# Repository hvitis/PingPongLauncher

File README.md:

# Ping Pong Launcher

A static website with four launcher tabs: the supplied 3D-printed launcher, [codyhsu’s Arduino launcher](https://www.mobile01.com/topicdetail.php?f=696&t=5867234), PingPongThrower (Pico 2 W), and [Nguyen Van Hien’s Bluetooth Table Tennis Robot](https://www.youtube.com/watch?v=-pSiuAdUKP4).

The original launcher has a complete build guide. It includes English source translations, an interactive Three.js CAD viewer, a 13-step animated assembly wizard, a parts list, and printable model downloads.

**Build status:** documented prototype. The source includes a physical prototype, but this English guide has not been validated through a complete build. Resolve the [open build questions](docs/build-notes.md) before ordering or operating the hardware.

## How the ball-throwing mechanism works

The launch energy comes from **two motor-driven, rubber-covered wheels**. Their rotating mass stores energy. Friction transfers some of that energy to the ball when it passes between their rims.

The “exhaust” is the **outlet tube**. It guides the ball toward the wheel contact region and the exit. The wheels provide the throwing force.

```mermaid
flowchart LR
    H[Hopper: gravity feeds balls] --> F[Geared feed screw: advances balls]
    F --> S[Stopper: holds the following ball]
    S --> W[Two rubber-covered wheels: accelerate one ball]
    W --> O[Outlet: ball leaves toward the table]
    C1[Left PWM control] --> W
    C2[Right PWM control] --> W
    C3[Feed PWM control] --> F
```

1. **The hopper stores the balls.** Gravity brings a ball to the feed opening.
2. **The geared motor turns the feed screw.** The screw advances balls toward the launch head.
3. **The stopper separates consecutive balls.** It helps prevent one ball from dragging the following ball into the wheels.
4. **The two wheel surfaces grip the ball.** Both contact surfaces move toward the exit, although the wheels rotate in opposite directions.
5. **The ball accelerates through friction.** Rubber improves traction and provides compliance at contact.
6. **The ball leaves the wheel contact region.** Its momentum carries it forward. The tilt angle sets the initial launch direction.

The feeder meters balls into the launch region. It is separate from the wheel mechanism that supplies launch energy. The feeder PWM mainly changes the feed interval. The other two PWM controls change the two launch motors independently.

### Speed, grip, and spin

A wheel’s rim speed depends on its radius and measured rotational speed:

```text
rim speed v = 2 × π × wheel radius r × rpm / 60
```

Use meters for `r` to obtain meters per second. The real exit speed also depends on contact pressure, rubber, slip, wheel inertia, motor torque, and speed loss during a shot. A PWM knob position is not a measured rpm or ball speed.

For an ideal pair of opposing, parallel wheel contacts with no slip, ball translation is approximately the average of the two contact speeds. The difference produces spin:

```text
ideal ball speed ≈ (v1 + v2) / 2
ideal spin rate  ≈ (v1 - v2) / (2 × ball radius)  [radians per second]
```

These equations describe a simplified contact model, not a calibrated prediction for this CAD. Actual contact angles, rubber compression, and slip change the result. Similar contact speeds reduce differential spin in that model. Unequal speeds add spin about the axis determined by the wheel arrangement.

The source does not specify the final rubber thickness, wheel gap, motor rpm, exit speed, or spin calibration. Measure those values during a guarded physical build. [The website](docs/index.html) explains the ball path alongside the model.

## Start the local website

Use Node.js 22 or newer. The website and development server require **no package installation**.

```sh
make serve
```

Open **http://127.0.0.1:4173**. `make serve` regenerates and validates the current site before opening the preview server. The server watches `docs/` and reloads the browser after a change. An edit to `docs/data/project.json` also regenerates the written guide and BOM.

```sh
make serve PORT=4200   # choose another local port
make build             # regenerate, check, and export dist/
make check             # regenerate and validate current content
npm run check        # check content, links, inventory, and GLB structure
npm run build        # regenerate documentation and copy the site to dist/
```

The local server binds to `127.0.0.1` by default. The exported site has no server requirement. All Three.js modules, models, photos, and fonts are local; there are no runtime CDN requests.

## Arduino launcher study

Open `?launcher=mobile01` to link directly to the second tab. Arrow keys, Home and End switch tabs; the URL supports reload and browser Back/Forward. Old section links still open the printed launcher.

Read [the analysis and design notes](docs/mobile01-analysis.md). The new diagrams explain the mechanism and a proposed electrical arrangement; they do not claim original CAD dimensions or verified original GPIO assignments. The KiCad download is an **unrouted placement draft**, with pads and named nets. It has no fabrication outputs and has not passed KiCad DRC or a physical build.

`docs/data/mobile01.json` records the parts and proposed connection map. The matching table and CSV files are maintained alongside it. Regenerate the three SVG diagrams, PCB and pad netlist with `python3 scripts/create-mobile01-assets.py`; the normal Node-only build uses the checked-in outputs.

## Bluetooth table tennis robot study

Open `?launcher=hien` to link directly to the fourth tab (Nguyen Van Hien's project).

Read [the technical analysis report](docs/hien-analysis.md). The tab features:
- **Interactive mechanism exploration:** 5-step animated ball flow showing bucket gravity fill, agitator stirring, servo escapement metering, curved feed drop, DT750 twin-flywheel launch, and pan/tilt trajectory vectoring.
- **Shot mode & spin comparison:** 4 practice drills (Service, Attack, Backspin Chop, Oscillating Swing) reconstructed from the creator's custom iOS BLE app.
- **Synchronized BOM & Wiring tables:** 21 parts with evidence ratings, and 14 connection rows downloadable as CSVs (`docs/downloads/hien-parts.csv` and `docs/downloads/hien-connections.csv`).
- **Vector technical diagrams:** Native SVGs for the mechanism (`docs/assets/hien/mechanism.svg`), electrical schematic with ATX split power rails and Mega GPIO assignments (`docs/assets/hien/schematic.svg`), and KiCad breakout board placement (`docs/assets/hien/pcb.svg`).
- **Unrouted KiCad placement draft:** 85 × 60 mm dual-layer board (`docs/downloads/hien-servo-breakout.kicad_pcb`) and netlist CSV (`docs/downloads/hien-pcb-netlist.csv`). Regenerate assets using `python3 scripts/create-hien-assets.py`.

## Build the launcher

Start with [the full English assembly guide](docs/assembly-guide.md). Use the website wizard to explore the CAD groups and track your checks on the current device.

| Build resource                           | File                                                                                       |
| ---------------------------------------- | ------------------------------------------------------------------------------------------ |
| Shopping checklist                       | [Website-ready checklist](docs/shopping-list.md) · [CSV](docs/downloads/shopping-list.csv) |
| Hardware and tools                       | [English BOM](docs/hardware-bom.md) · [CSV](docs/downloads/hardware-bom.csv)               |
| Component image sources                  | [Photo references and rights](docs/component-image-sources.md)                             |
| Print settings, orientations, and plates | [Print guide](docs/print-guide.md)                                                         |
| English print project                    | [28 objects on 10 plates](docs/downloads/launcher-english.3mf)                             |
| Individual STL files                     | [ZIP, organized by plate](docs/downloads/launcher-stl-pack.zip)                            |
| Editable CAD                             | [STEP assembly](docs/downloads/launcher-assembly.step)                                     |
| Wiring and first power-on                | [DC topology and checks](docs/wiring-guide.md)                                             |
| English annotations and terminology      | [Source translation](docs/translation.md)                                                  |
| Offline written instructions             | [Guide ZIP with reference photos](docs/downloads/english-build-guide.zip)                  |
| Missing details and source differences   | [Build notes](docs/build-notes.md)                                                         |

The source specifies two 12 V 550 motors, one 12 V / 77 rpm geared motor, three PWM controllers, four 7 × 16 × 5 mm bearings, and a 12 V / 3 A supply. These are source specifications, not a verified motor-current budget. The CAD and spreadsheet disagree on some screw lengths and tilt hardware.

The print project stores a Bambu Lab A1 mini profile, a 0.4 mm nozzle, 0.20 mm layers, four walls, 25% infill, and manual tree supports. All 28 objects use slot 1, saved as PETG. Select your actual printer and material before slicing. Inspect the original orientations and painted supports.

WARNING: Disconnect power before assembly or adjustment. Wait for all moving parts to stop.

WARNING: Fit guards around accessible wheels, gears, and the feeder before operation. Keep hands clear of pinch points.

## Edit quickly

The project uses native browser modules and a small Node server. Content and behavior are separated.

```text
docs/
  index.html                 Page structure and fixed explanatory sections
  styles.css                 Responsive styles and reduced-motion handling
  app.js                     Parts filters, plate cards, and viewer setup
  viewer.js                  Three.js loading, picking, orbiting, and animation
  wizard.js                  Steps, navigation, and browser-local progress
  shopping.js                Shopping checklist and gathered-item progress
  storage.js                 Shared storage helpers with failure handling
  data/project.json          Main editable content: BOM, tools, checks, steps
  data/print-inventory.json  Generated geometry and plate report
  assets/                    Local GLB, photos, plate previews, and video
  downloads/                 English 3MF, STL pack, STEP, CSV, and guide ZIP
  vendor/                    Pinned Three.js 0.180.0 modules and license
scripts/
  serve.mjs                  Local preview and live reload
  generate-docs.mjs          Written guides, BOM, and deterministic document ZIP
  check.mjs                  Content, link, module, and asset checks
  build.mjs                  Generate, check, export to dist/
  import-step.mjs            Optional CAD tessellation
  create-viewer-model.mjs    Optional conversion to grouped GLB
  prepare-assets.py          Optional STL and inventory regeneration
```

Edit `project.json` for parts and assembly content. It feeds both the website and generated Markdown. Do not edit generated `assembly-guide.md`, `hardware-bom.md`, `print-guide.md`, or `build-notes.md` directly. Edit their content or generator template instead. Translation, wiring, and attribution documents are maintained directly.

The GLB contains 101 meshes from the actual supplied STEP. Both viewers share one model request and use separate scenes and materials. Off-screen rendering pauses. Animation respects reduced-motion preferences. A reference image and written instructions remain available when WebGL fails.

### Optional model regeneration

Normal content edits do not require CAD conversion or Python. To regenerate geometry, install `occt-import-js@0.0.23` for development and NumPy for the Python mesh exporter. For example, use `npm install --no-save occt-import-js@0.0.23` in a development checkout. Then run:

```sh
node scripts/import-step.mjs
node scripts/create-viewer-model.mjs
python3 scripts/prepare-assets.py
npm run build
```

The tools read the retained English-named CAD and 3MF. The Python exporter preserves source build orientations. Mesh closure checks do not establish printability, physical fit, wall thickness, or safe operating speed.

### Optional browser checks

Run `npm ci`, then `npx playwright install chromium`. Run `npm test` while the preview server is running, or `npm run test:ci` to build and test the static export without a server. `BASE_URL` selects a different preview URL. `PLAYWRIGHT_MODULE` can point to an existing Playwright module. The script checks desktop/mobile layout, wizard progress, filters, the model, reduced motion, and the image fallback.

## GitHub Pages

The repository includes [a Pages deployment workflow](.github/workflows/pages.yml). It runs on every pushed tag and by manual dispatch. A branch push alone does not deploy. It uses the [official GitHub Pages workflow](https://docs.github.com/en/pages/getting-started-with-github-pages/using-custom-workflows-with-github-pages).

1. Create or select a GitHub repository.
2. Initialize this folder with `git init -b main` if necessary.
3. Commit the files and push the `main` branch to that repository.
4. Open **Settings → Pages**.
5. Select **GitHub Actions** as the publishing source.
6. Allow tag deployments in the `github-pages` environment if deployment restrictions are enabled.
7. Create and push a tag, or run **Deploy build guide to GitHub Pages** manually.
8. Open the URL reported by the deployment job.

For example, after committing the current files:

```sh
git tag v1.0.0
git push origin v1.0.0
```

The workflow checks and builds the tagged commit, runs both browser suites against `dist/`, tests firmware logic, and creates a GitHub Release with a static-site ZIP after deployment. Each tag has its own workflow concurrency group, so a later tag does not cancel an earlier tag run. The site is one shared deployment; avoid pushing release tags out of order.

All site paths are relative, so a project URL such as `/PingPongLauncher/` works. The workflow uploads only `dist/`. It does not publish development dependencies or original input folders.

No hosted deployment is implied by these instructions. Publishing requires working GitHub authentication. Confirm redistribution rights for the supplied hardware and media before making a public repository.

## Future iterations

The next useful iteration is a documented physical build: resolve fasteners, measure currents and fits, and replace inferred steps with confirmed photographs. Follow that with guards, a verified DC system, an updated outlet/stopper, replaceable balanced tires, and measured speed control. See [FUTURE.md](FUTURE.md) for priorities and completion evidence.

## Sources and rights

The Chinese-named input files and duplicate STEP are removed after verification, as requested. Their useful contents remain as English-named CAD, print files, media, and translations. Historical filenames and SHA-256 hashes remain in [the source manifest](docs/data/source-manifest.json).

The source designer and hardware/media license are unknown. The MIT license covers newly written website and tooling code only. See [sources and rights](docs/attribution.md). Three.js retains its own MIT license. The source video audio is unchanged and has not been transcribed; English captions describe the visible mechanism.

## PingPongThrower

Open `?launcher=thrower` for the third tab: native simulation, five test phases, parts, wiring (including the 3D cable explorer), assembly and print downloads. The port uses isolated shadow DOM views styled with the app theme. `docs/thrower/` is the single maintained source for this project: edit its viewer modules, JSON, CAD, firmware and resources directly. Optional CAD and wiring tools are retained in `docs/thrower/tools/`. The build uses existing meshes and print files and needs no CAD tools.

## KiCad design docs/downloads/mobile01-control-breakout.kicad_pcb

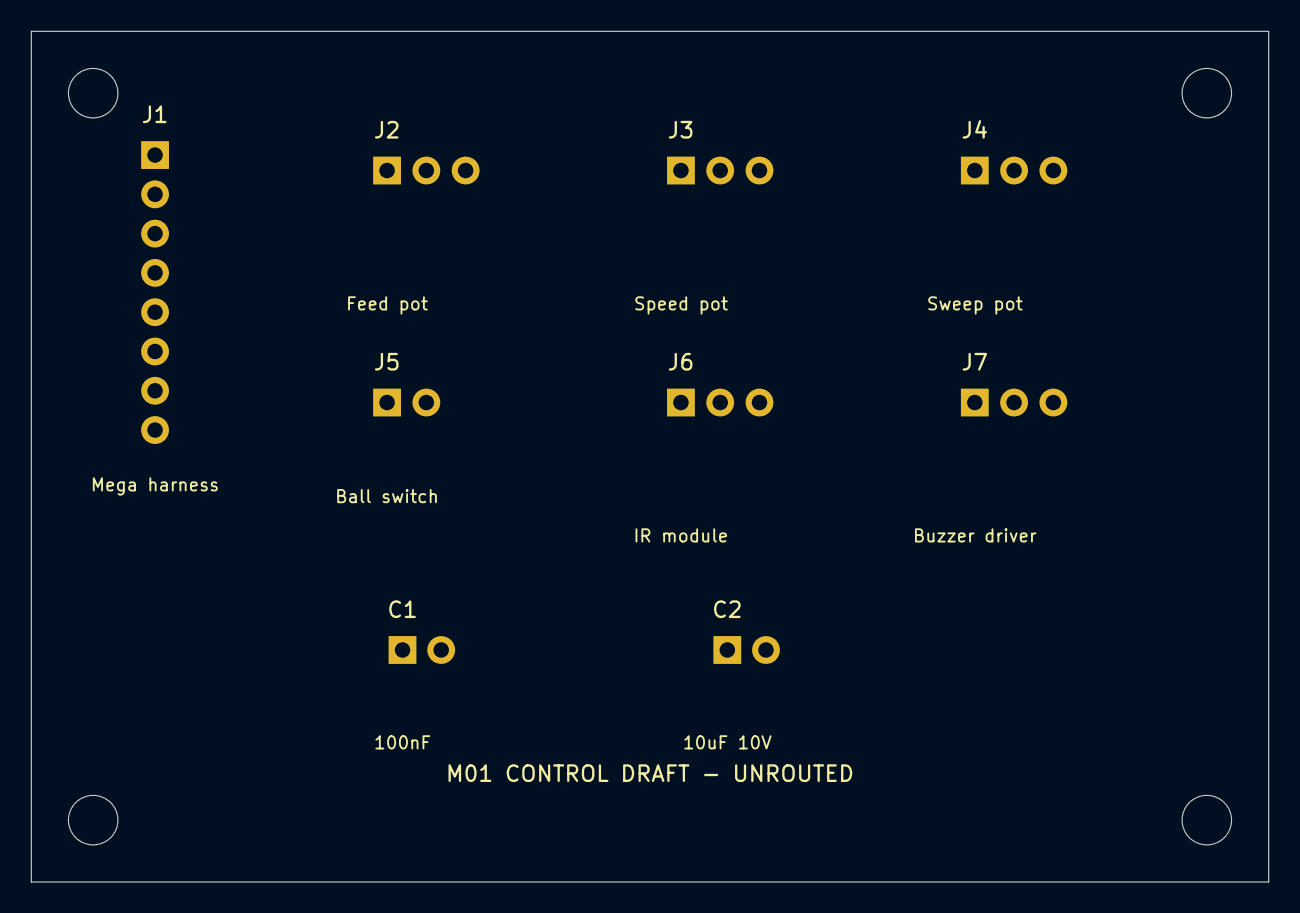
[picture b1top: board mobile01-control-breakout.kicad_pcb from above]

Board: 2 copper layers, 80.0 x 55.0 mm, 9 parts (0 on the bottom side), 8 nets, no tracks yet.

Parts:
C1: 100nF; C_Disc_D5.0mm_W2.5mm_P2.50mm
C2: 10uF 10V; CP_Radial_D5.0mm_P2.50mm
J1: Mega harness; PinHeader_1x08_P2.54mm_Vertical
J2: Feed pot; PinHeader_1x03_P2.54mm_Vertical
J3: Speed pot; PinHeader_1x03_P2.54mm_Vertical
J4: Sweep pot; PinHeader_1x03_P2.54mm_Vertical
J5: Ball switch; PinHeader_1x02_P2.54mm_Vertical
J6: IR module; PinHeader_1x03_P2.54mm_Vertical
J7: Buzzer driver; PinHeader_1x03_P2.54mm_Vertical

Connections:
+5V_LOGIC: C1.1, C2.1, J1.2, J2.3, J3.3, J4.3, J6.2, J7.2
BALL_D22: J1.6, J5.2
FEED_A0: J1.3, J2.2
GND: C1.2, C2.2, J1.1, J2.1, J3.1, J4.1, J5.1, J6.1, J7.1
IR_D24: J1.7, J6.3
SPEED_A1: J1.4, J3.2
SWEEP_A2: J1.5, J4.2
TONE_D26: J1.8, J7.3

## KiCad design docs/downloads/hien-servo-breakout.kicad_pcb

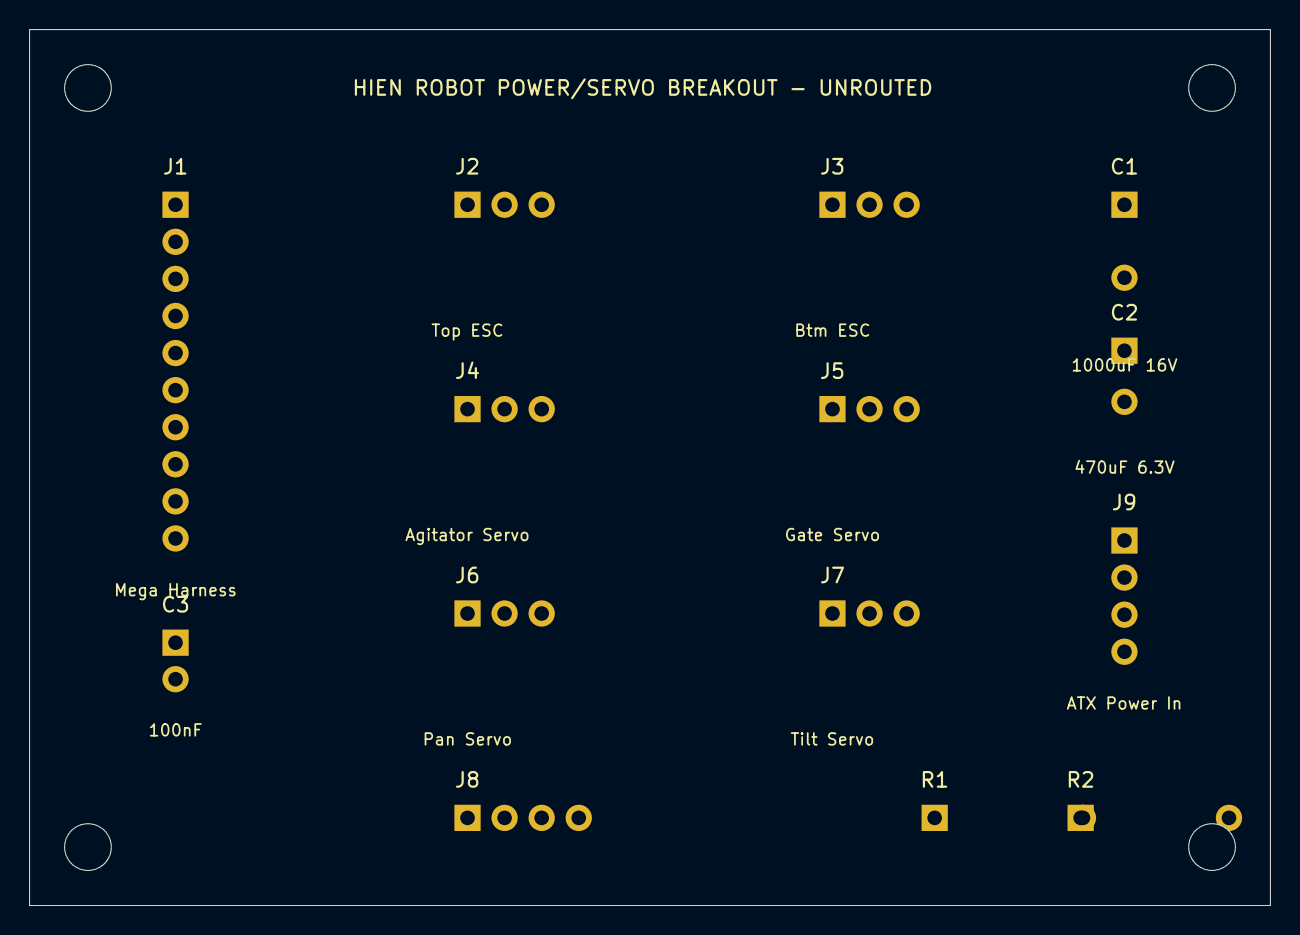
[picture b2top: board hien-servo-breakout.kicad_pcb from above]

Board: 2 copper layers, 85.0 x 60.0 mm, 14 parts (0 on the bottom side), 13 nets, no tracks yet.

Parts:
C1: 1000uF 16V; CP_Radial_D10.0mm_P5.00mm
C2: 470uF 6.3V; CP_Radial_D8.0mm_P3.50mm
C3: 100nF; C_Disc_D5.0mm_W2.5mm_P2.50mm
J1: Mega Harness; PinHeader_1x10_P2.54mm_Vertical
J2: Top ESC; PinHeader_1x03_P2.54mm_Vertical
J3: Btm ESC; PinHeader_1x03_P2.54mm_Vertical
J4: Agitator Servo; PinHeader_1x03_P2.54mm_Vertical
J5: Gate Servo; PinHeader_1x03_P2.54mm_Vertical
J6: Pan Servo; PinHeader_1x03_P2.54mm_Vertical
J7: Tilt Servo; PinHeader_1x03_P2.54mm_Vertical
J8: HM-10 BLE; PinHeader_1x04_P2.54mm_Vertical
J9: ATX Power In; PinHeader_1x04_P2.54mm_Vertical
R1: 1k Divider; R_Axial_DIN0207_L6.3mm_D2.5mm_P10.16mm_Horizontal
R2: 2k Divider; R_Axial_DIN0207_L6.3mm_D2.5mm_P10.16mm_Horizontal

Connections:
+5V_ATX: C2.1, J4.2, J5.2, J6.2, J7.2, J9.4
+5V_LOGIC: C3.1, J1.2, J8.2
+12V_ATX: C1.1, J9.1
AGIT_SERVO_D4: J1.5, J4.3
BLE_RX1_D19: J1.10, J8.3
BLE_RX_3V3: J8.4, R1.2, R2.1
BLE_TX1_D18: J1.9, R1.1
ESC_BTM_D3: J1.4, J3.3
ESC_TOP_D2: J1.3, J2.3
GATE_SERVO_D5: J1.6, J5.3
GND: C1.2, C2.2, C3.2, J1.1, J2.1, J2.2, J3.1, J3.2, J4.1, J5.1, J6.1, J7.1, J8.1, J9.2, J9.3, R2.2
PAN_SERVO_D6: J1.7, J6.3
TILT_SERVO_D7: J1.8, J7.3
